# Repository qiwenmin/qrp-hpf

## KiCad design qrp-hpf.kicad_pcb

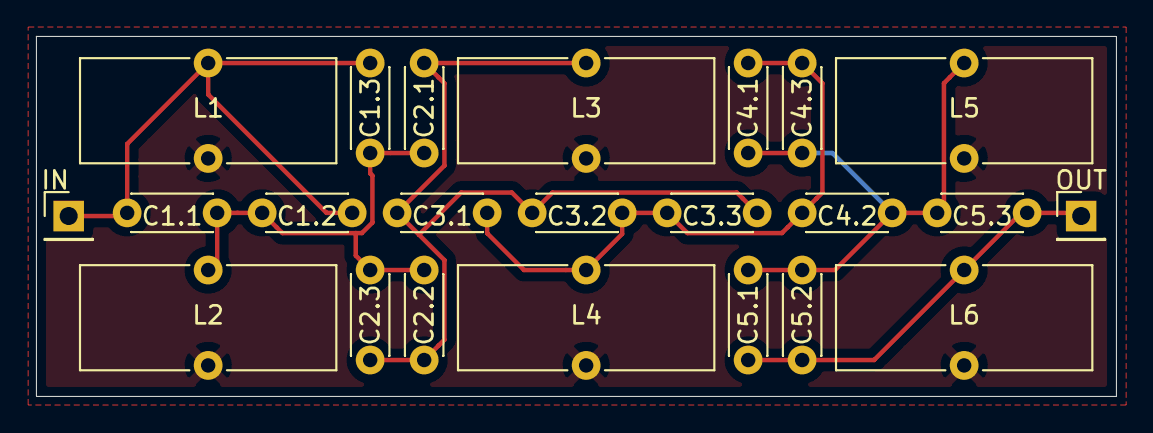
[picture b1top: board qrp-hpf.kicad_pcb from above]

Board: 2 copper layers, 60.0 x 20.0 mm, 23 parts (0 on the bottom side), 7 nets.

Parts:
C1.1, C5.1: 330p; C_Disc_D4.3mm_W1.9mm_P5.00mm
C1.2, C1.3, C3.1, C5.2, C5.3: 470p; C_Disc_D4.3mm_W1.9mm_P5.00mm
C2.1, C4.1: 20p; C_Disc_D4.3mm_W1.9mm_P5.00mm
C2.2, C4.2: 56p; C_Disc_D4.3mm_W1.9mm_P5.00mm
C2.3, C4.3: 1000p; C_Disc_D4.3mm_W1.9mm_P5.00mm
C3.2: 560p; C_Disc_D4.3mm_W1.9mm_P5.00mm
C3.3: 0p; C_Disc_D4.3mm_W1.9mm_P5.00mm
J1: IN; PinHeader_1x01_P2.54mm_Vertical
J2: OUT; PinHeader_1x01_P2.54mm_Vertical
L1, L6: 5.66u; L_Toroid_Vertical_L14.0mm_W5.6mm_P5.30mm_Bourns_5700
L2, L5: 2.59u; L_Toroid_Vertical_L14.0mm_W5.6mm_P5.30mm_Bourns_5700
L3, L4: 2.37u; L_Toroid_Vertical_L14.0mm_W5.6mm_P5.30mm_Bourns_5700

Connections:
GND: L1.2, L2.2, L3.2, L4.2, L5.2, L6.2
IN: C1.1.2, C1.2.2, C1.3.2, J1.1, L1.1
unnamed: C1.1.1, C1.2.1, C1.3.1, C2.1.2, C2.2.2, C2.3.2, L2.1
unnamed: C2.1.1, C2.2.1, C2.3.1, C3.1.2, C3.2.2, C3.3.2, L3.1
unnamed: C3.1.1, C3.2.1, C3.3.1, C4.1.2, C4.2.2, C4.3.2, L4.1
unnamed: C4.1.1, C4.2.1, C4.3.1, C5.1.2, C5.2.2, C5.3.2, L5.1
OUT: C5.1.1, C5.2.1, C5.3.1, J2.1, L6.1

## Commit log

2019-05-08 Initial commit.
2019-07-08 Add dimensions.
